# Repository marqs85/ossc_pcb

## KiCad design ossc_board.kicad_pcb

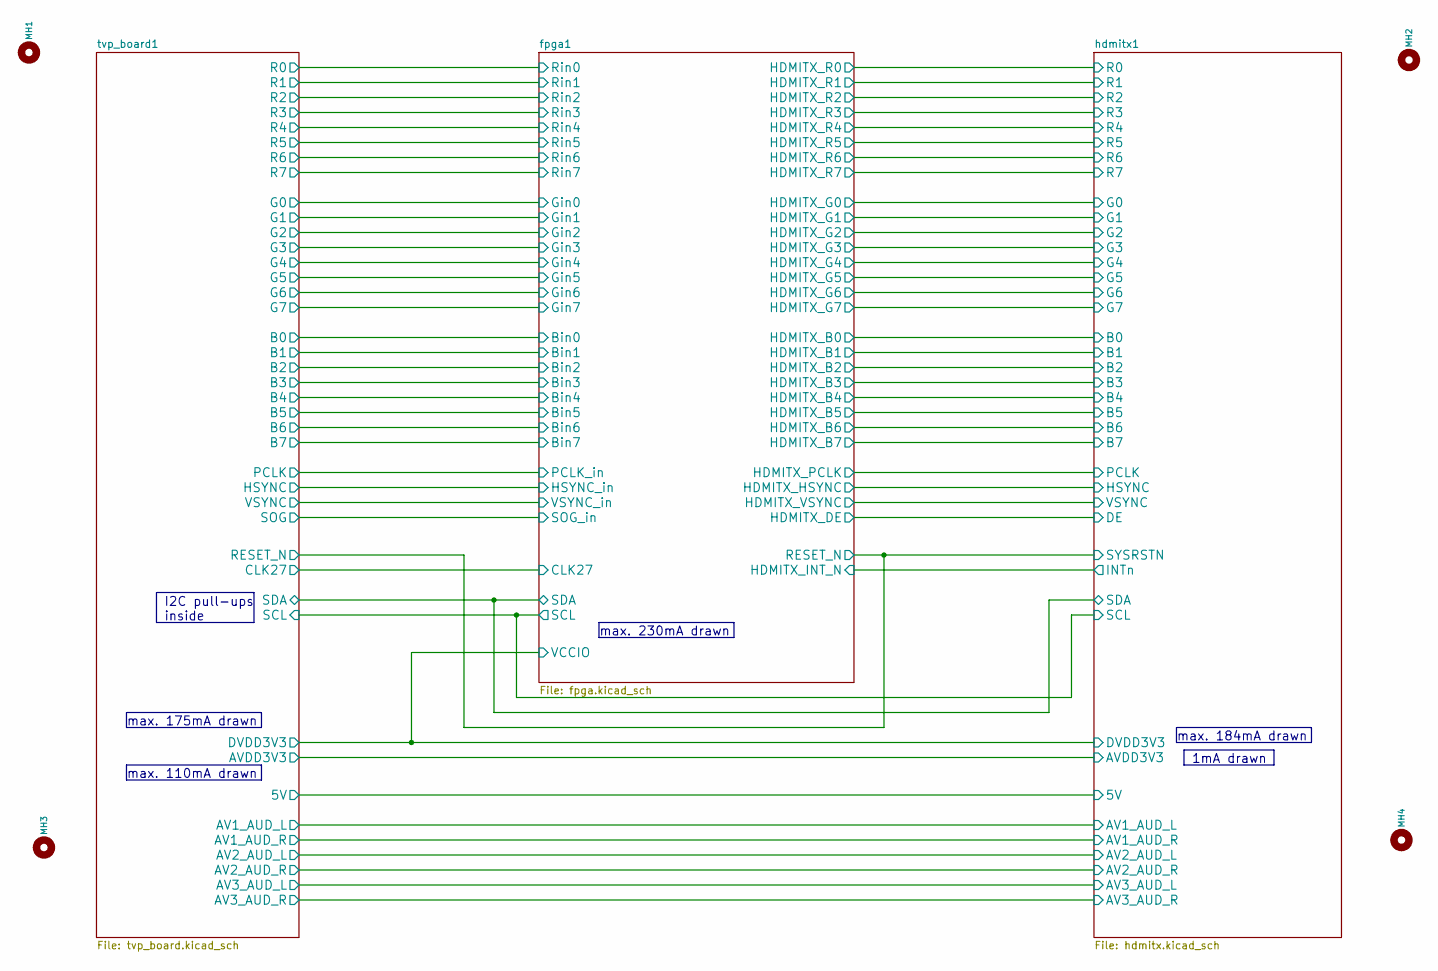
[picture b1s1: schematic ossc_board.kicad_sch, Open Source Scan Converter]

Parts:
MH1, MH2, MH3, MH4: CONN_1; 1pin

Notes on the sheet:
1mA drawn
max. 230mA drawn
max. 184mA drawn
max. 110mA drawn
max. 175mA drawn
I2C pull-ups inside

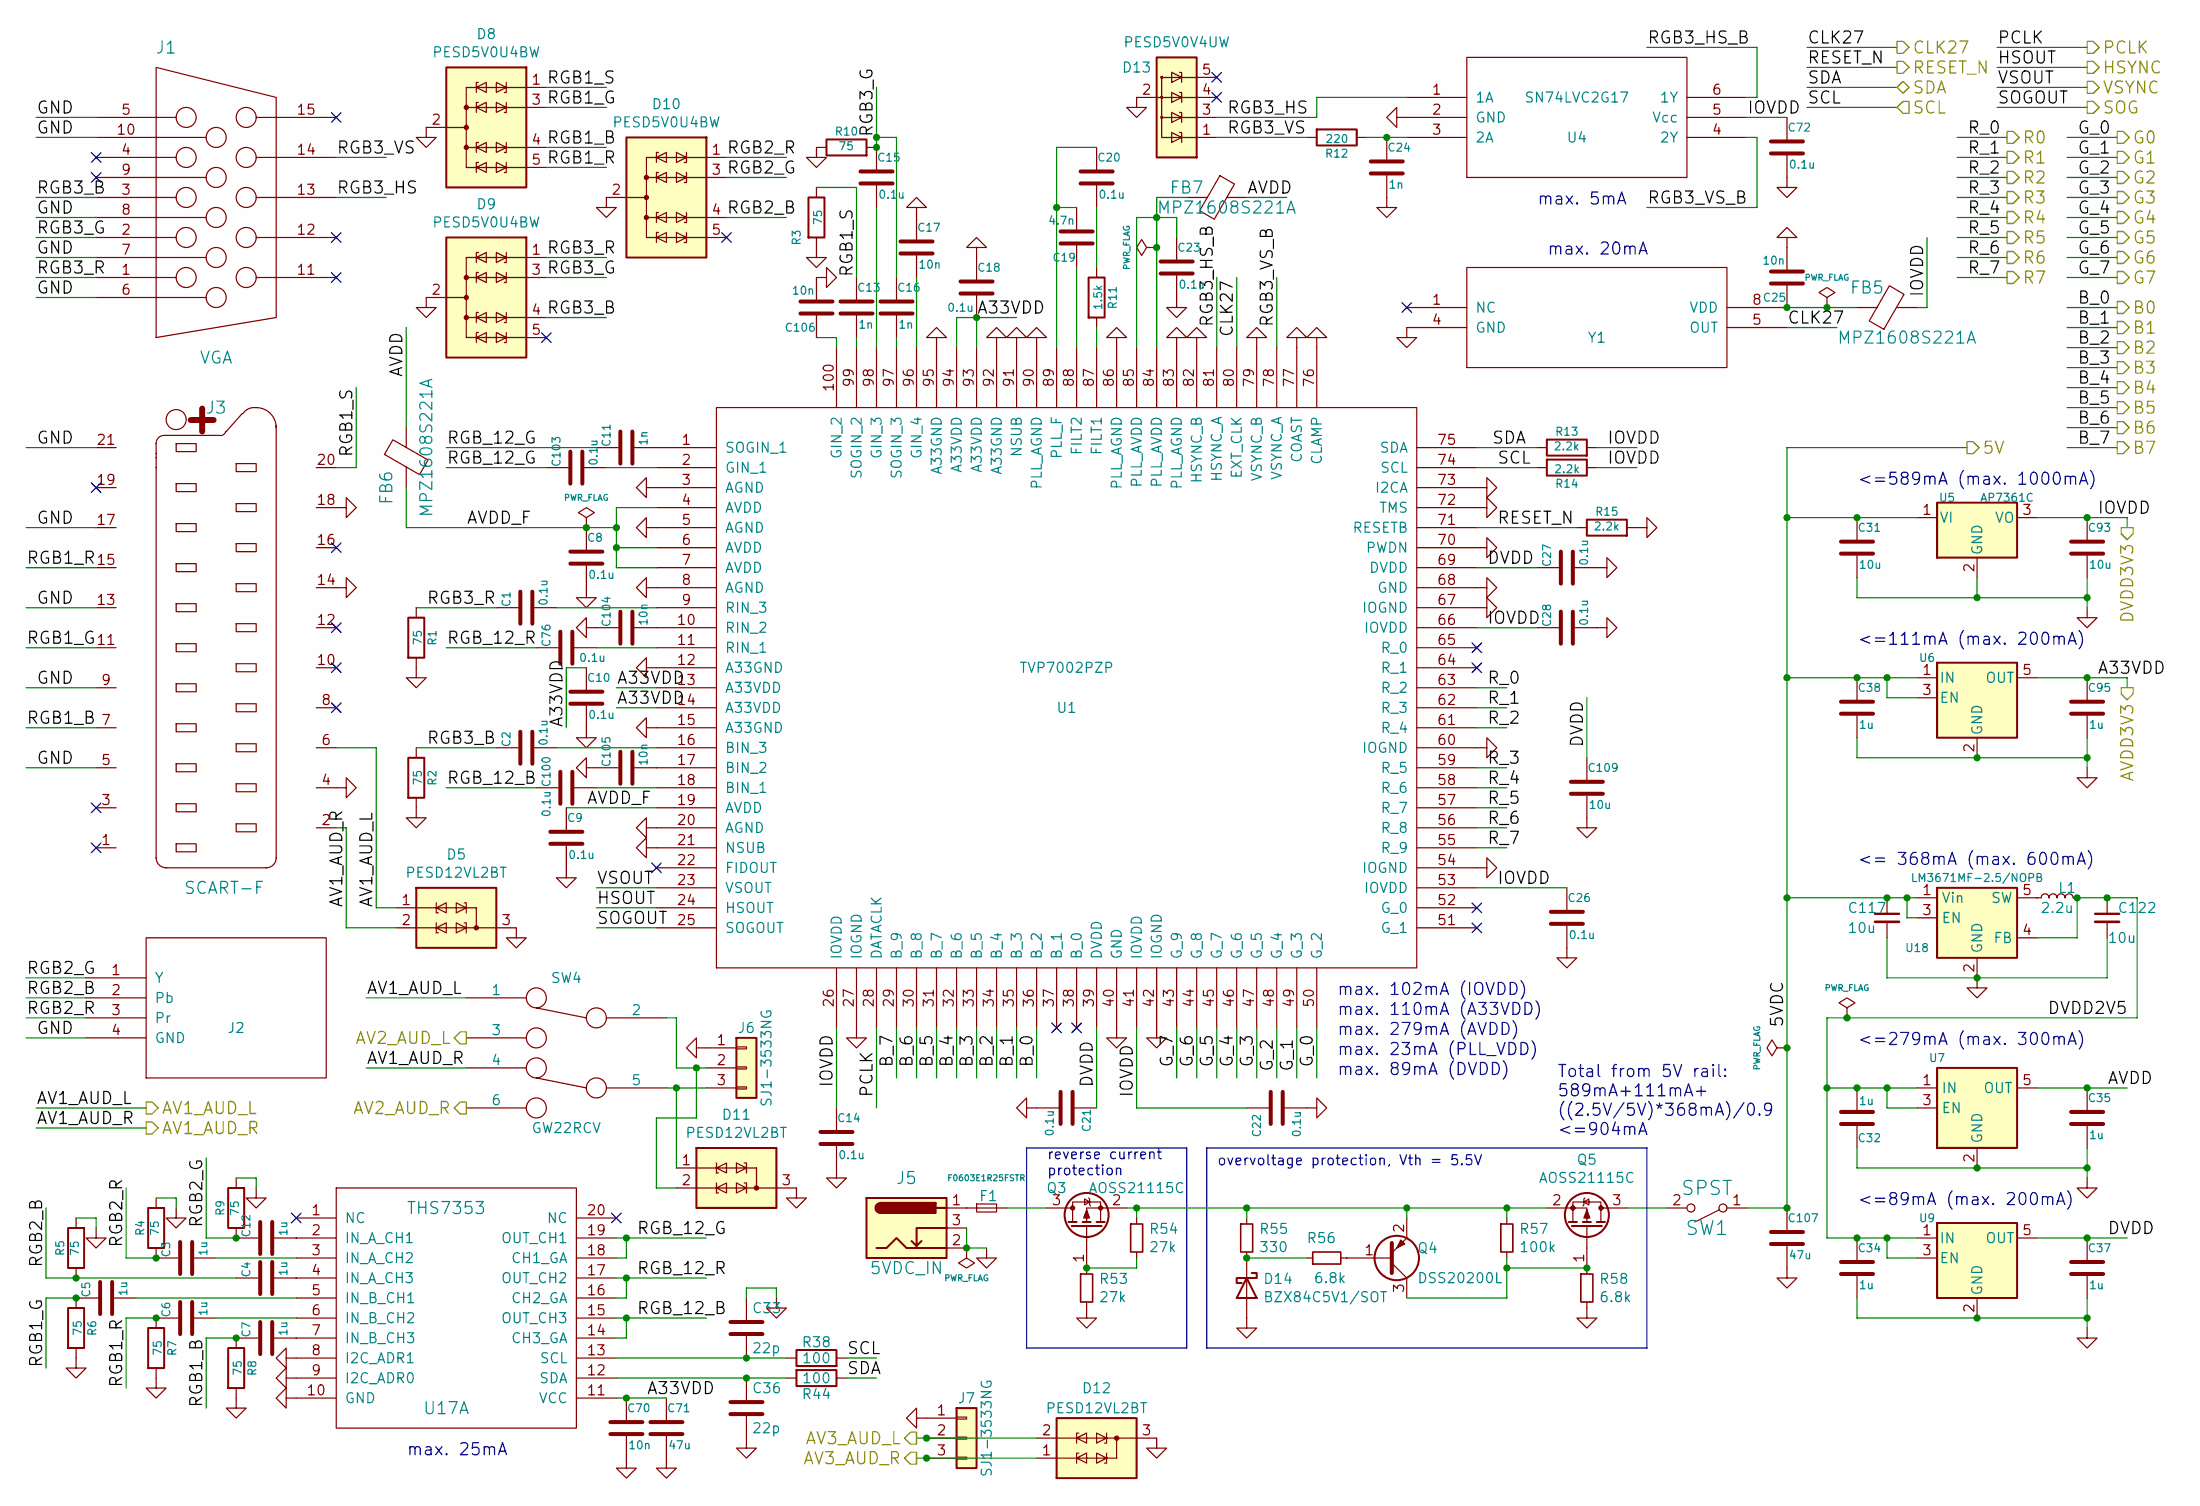
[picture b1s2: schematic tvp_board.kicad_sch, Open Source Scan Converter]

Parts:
C1, C2, C8, C9, C10, C14, C15, C18, C20, C21, C22, C23, C26, C27, C28, C72, C76, C100, C103: 0.1u; SM0603_Capa_libcms
C3, C4, C5, C6, C7, C12, C32, C34, C35, C37, C38, C95: 1u; SM0603_Capa_libcms
C11, C13, C16, C24: 1n; SM0603_Capa_libcms
C17, C25, C70, C104, C105, C106: 10n; SM0603_Capa_libcms
C19: 4.7n; SM0603_Capa_libcms
C31, C93, C109, C117, C122: 10u; SM0603_Capa_libcms
C33, C36: 22p; SM0603_Capa_libcms
C71, C107: 47u; SM0805_libcms
D5, D11, D12: PESD12VL2BT; SOT-23_Handsoldering
D8, D9, D10: PESD5V0U4BW; SOT-665
D13: PESD5V0V4UW; SOT-665
D14: BZX84C5V1/SOT; D_SOT-23_ANK
F1: F0603E1R25FSTR; SM0603_Resistor_libcms
FB5, FB6, FB7: MPZ1608S221A; SM0603_Resistor_libcms
J1: VGA; VGA_CONN
J2: (no value)
J3: SCART-F; SCART_CONN
J5: 5VDC_IN; BARREL_JACK_roundconn
J6, J7: SJ1-3533NG
L1: 2.2u; CDRH2D14
Q3, Q5: AOSS21115C; SOT-23_Handsoldering
Q4: DSS20200L; SOT-23_Handsoldering
R1, R2, R3, R4, R5, R6, R7, R8, R9, R10: 75; SM0603_Resistor_libcms
R11: 1.5k; SM0603_Resistor_libcms
R12: 220; SM0603_Resistor_libcms
R13, R14, R15: 2.2k; SM0603_Resistor_libcms
R38, R44: 100; SM0603_Resistor_libcms
R53, R54: 27k; SM0603_Resistor_libcms
R55: 330; SM0805_libcms
R56, R58: 6.8k; SM0603_Resistor_libcms
R57: 100k; SM0603_Resistor_libcms
SW1: SPST; SW_SPDT
SW4: GW22RCV; GW22RxV
U1: TVP7002PZP; TQFP-100_thermal
U4: SN74LVC2G17; SOT-23-6_Handsoldering
U5: AP7361C; SOT-223_Handsoldering
U6, U7, U9: (no value)
U17: THS7353; TSSOP-20_4.4x6.5mm_Pitch0.65mm_Handsoldering
U18: LM3671MF-2.5/NOPB; SOT-23-5_Handsoldering
Y1: (no value)

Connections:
/fpga1/CLK27: U1.80 (EXT_CLK), Y1.5 (OUT); also elsewhere on the board
/fpga1/RESET_N: R15.1, U1.71 (RESETB); also elsewhere on the board
/fpga1/SCL: R14.2, R38.2, U1.74 (SCL); also elsewhere on the board
/fpga1/SDA: R13.1, R44.1, U1.75 (SDA); also elsewhere on the board
/hdmitx1/5V: C31.1, C38.1, C107.1, C117.1, SW1.1 (A), U5.1 (VI), U6.1 (IN), U6.3 (EN), U18.1 (Vin), U18.3 (EN); also elsewhere on the board
/hdmitx1/AV1_AUD_L: D5.1 (TVS1), J3.6, SW4.1; also elsewhere on the board
/hdmitx1/AV1_AUD_R: D5.2 (TVS2), J3.2, SW4.4; also elsewhere on the board
/hdmitx1/AV2_AUD_L: SW4.3; also elsewhere on the board
/hdmitx1/AV2_AUD_R: SW4.6; also elsewhere on the board
/hdmitx1/AV3_AUD_L: D12.2 (TVS2), J7.2; also elsewhere on the board
/hdmitx1/AV3_AUD_R: D12.1 (TVS1), J7.3; also elsewhere on the board
/hdmitx1/AVDD3V3: C10.1, C18.2, C70.1, C71.1, C95.1, U1.13 (A33VDD), U1.14 (A33VDD), U1.93 (A33VDD), U1.94 (A33VDD), U6.5 (OUT), U17.11 (VCC); also elsewhere on the board
/hdmitx1/DVDD3V3: C14.1, C22.1, C26.1, C28.1, C72.1, C93.1, FB5.2, R13.2, R14.1, U1.26 (IOVDD), U1.41 (IOVDD), U1.53 (IOVDD), U1.66 (IOVDD), U4.5 (Vcc), U5.3 (VO); also elsewhere on the board
/tvp_board1/AVDD: C35.1, FB6.1, FB7.1, U7.5 (OUT)
/tvp_board1/AVDD_F: C8.1, C9.1, FB6.2, U1.4 (AVDD), U1.6 (AVDD), U1.7 (AVDD), U1.19 (AVDD)
/tvp_board1/B0: U1.36 (B_2); also elsewhere on the board
/tvp_board1/B1: U1.35 (B_3); also elsewhere on the board
/tvp_board1/B2: U1.34 (B_4); also elsewhere on the board
/tvp_board1/B3: U1.33 (B_5); also elsewhere on the board
/tvp_board1/B4: U1.32 (B_6); also elsewhere on the board
/tvp_board1/B5: U1.31 (B_7); also elsewhere on the board
/tvp_board1/B6: U1.30 (B_8); also elsewhere on the board
/tvp_board1/B7: U1.29 (B_9); also elsewhere on the board
/tvp_board1/DVDD: C21.1, C27.1, C37.1, C109.1, U1.39 (DVDD), U1.69 (DVDD), U9.5 (OUT)
/tvp_board1/DVDD2V5: C32.2, C34.1, C122.1, L1.2, U7.1 (IN), U7.3 (EN), U9.1 (IN), U9.3 (EN), U18.4 (FB)
/tvp_board1/FID: U1.22 (FIDOUT); also elsewhere on the board
/tvp_board1/G0: U1.50 (G_2); also elsewhere on the board
/tvp_board1/G1: U1.49 (G_3); also elsewhere on the board
/tvp_board1/G2: U1.48 (G_4); also elsewhere on the board
/tvp_board1/G3: U1.47 (G_5); also elsewhere on the board
/tvp_board1/G4: U1.46 (G_6); also elsewhere on the board
/tvp_board1/G5: U1.45 (G_7); also elsewhere on the board
/tvp_board1/G6: U1.44 (G_8); also elsewhere on the board
/tvp_board1/G7: U1.43 (G_9); also elsewhere on the board
/tvp_board1/HSYNC: U1.24 (HSOUT); also elsewhere on the board
/tvp_board1/PCLK: U1.28 (DATACLK); also elsewhere on the board
/tvp_board1/R0: U1.63 (R_2); also elsewhere on the board
/tvp_board1/R1: U1.62 (R_3); also elsewhere on the board
/tvp_board1/R2: U1.61 (R_4); also elsewhere on the board
/tvp_board1/R3: U1.59 (R_5); also elsewhere on the board
/tvp_board1/R4: U1.58 (R_6); also elsewhere on the board
/tvp_board1/R5: U1.57 (R_7); also elsewhere on the board
/tvp_board1/R6: U1.56 (R_8); also elsewhere on the board
/tvp_board1/R7: U1.55 (R_9); also elsewhere on the board
/tvp_board1/RGB1_B: C7.1, D8.4 (TVS3), J3.7, R8.1
/tvp_board1/RGB1_G: C5.1, D8.3 (TVS2), J3.11, R6.1
/tvp_board1/RGB1_R: C6.1, D8.5 (TVS4), J3.15, R7.1
/tvp_board1/RGB1_S: C13.1, D8.1 (TVS1), J3.20, R3.1
/tvp_board1/RGB2_B: C4.1, D10.4 (TVS3), J2.2 (Pb), R5.1
/tvp_board1/RGB2_G: C12.1, D10.3 (TVS2), J2.1 (Y), R9.1
/tvp_board1/RGB2_R: C3.1, D10.1 (TVS1), J2.3 (Pr), R4.1
/tvp_board1/RGB3_B: C2.1, D9.4 (TVS3), J1.3 (BLUE), R2.1
/tvp_board1/RGB3_G: C15.1, C16.1, D9.3 (TVS2), J1.2 (GREEN), R10.2
/tvp_board1/RGB3_HS: D13.3 (IO2), J1.13 (HSYNC), U4.1 (1A)
/tvp_board1/RGB3_HS_B: U1.81 (HSYNC_A), U4.6 (1Y)
/tvp_board1/RGB3_R: C1.1, D9.1 (TVS1), J1.1 (RED), R1.1
/tvp_board1/RGB3_VS: D13.1 (IO1), J1.14 (VSYNC), R12.2
/tvp_board1/RGB3_VS_B: U1.78 (VSYNC_A), U4.4 (2Y)
/tvp_board1/RGB_12_B: C100.1, U17.14 (CH3_GA), U17.15 (OUT_CH3)
/tvp_board1/RGB_12_G: C11.1, C103.1, U17.18 (CH1_GA), U17.19 (OUT_CH1)
/tvp_board1/RGB_12_R: C76.1, U17.16 (CH2_GA), U17.17 (OUT_CH2)
/tvp_board1/VSYNC: U1.23 (VSOUT); also elsewhere on the board
unnamed: C1.2, U1.9 (RIN_3)
unnamed: C2.2, U1.16 (BIN_3)
unnamed: C3.2, U17.3 (IN_A_CH2)
unnamed: C4.2, U17.4 (IN_A_CH3)
unnamed: C5.2, U17.5 (IN_B_CH1)
unnamed: C6.2, U17.6 (IN_B_CH2)
unnamed: C7.2, U17.7 (IN_B_CH3)
unnamed: C11.2, U1.1 (SOGIN_1)
unnamed: C12.2, U17.2 (IN_A_CH1)
unnamed: C13.2, U1.99 (SOGIN_2)
unnamed: C15.2, U1.98 (GIN_3)
unnamed: C16.2, U1.97 (SOGIN_3)
unnamed: C17.2, U1.96 (GIN_4)
unnamed: C19.1, U1.88 (FILT2)
unnamed: C19.2, C20.1, U1.89 (PLL_F)
unnamed: C20.2, R11.1
unnamed: C23.1, FB7.2, U1.84 (PLL_AVDD), U1.85 (PLL_AVDD)
unnamed: C24.1, R12.1, U4.3 (2A)
unnamed: C25.1, FB5.1, Y1.8 (VDD)
unnamed: C33.2, R38.1, U17.13 (SCL)
unnamed: C36.1, R44.2, U17.12 (SDA)
unnamed: C76.2, U1.11 (RIN_1)
unnamed: C100.2, U1.18 (BIN_1)
unnamed: C103.2, U1.2 (GIN_1)
unnamed: C104.2, U1.10 (RIN_2)
unnamed: C105.2, U1.17 (BIN_2)
unnamed: C106.1, U1.100 (GIN_2)
unnamed: D11.1 (TVS1), J6.3, SW4.5
unnamed: D11.2 (TVS2), J6.2, SW4.2
unnamed: D14.1 (K), R55.2, R56.1
unnamed: F1.1, J5.1
unnamed: F1.2, Q3.3 (D)
unnamed: L1.1, U18.5 (SW)
unnamed: Q3.1 (G), R53.1, R54.2
unnamed: Q3.2 (S), Q4.2 (E), Q5.2 (S), R54.1, R55.1, R57.1
unnamed: Q4.1 (B), R56.2
unnamed: Q4.3 (C), Q5.1 (G), R57.2, R58.1
unnamed: Q5.3 (D), SW1.2 (B)
unnamed: R11.2, U1.87 (FILT1)

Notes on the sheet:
max. 25mA
<=589mA (max. 1000mA)
max. 20mA
<=279mA (max. 300mA)
max. 279mA (AVDD)
<=111mA (max. 200mA)
max. 23mA (PLL_VDD)
max. 89mA (DVDD)
max. 110mA (A33VDD)
reverse current protection
<= 368mA (max. 600mA)
Total from 5V rail: 589mA+111mA+ ((2.5V/5V)*368mA)/0.9 <=904mA
max. 102mA (IOVDD)
max. 5mA
overvoltage protection, Vth = 5.5V
<=89mA (max. 200mA)

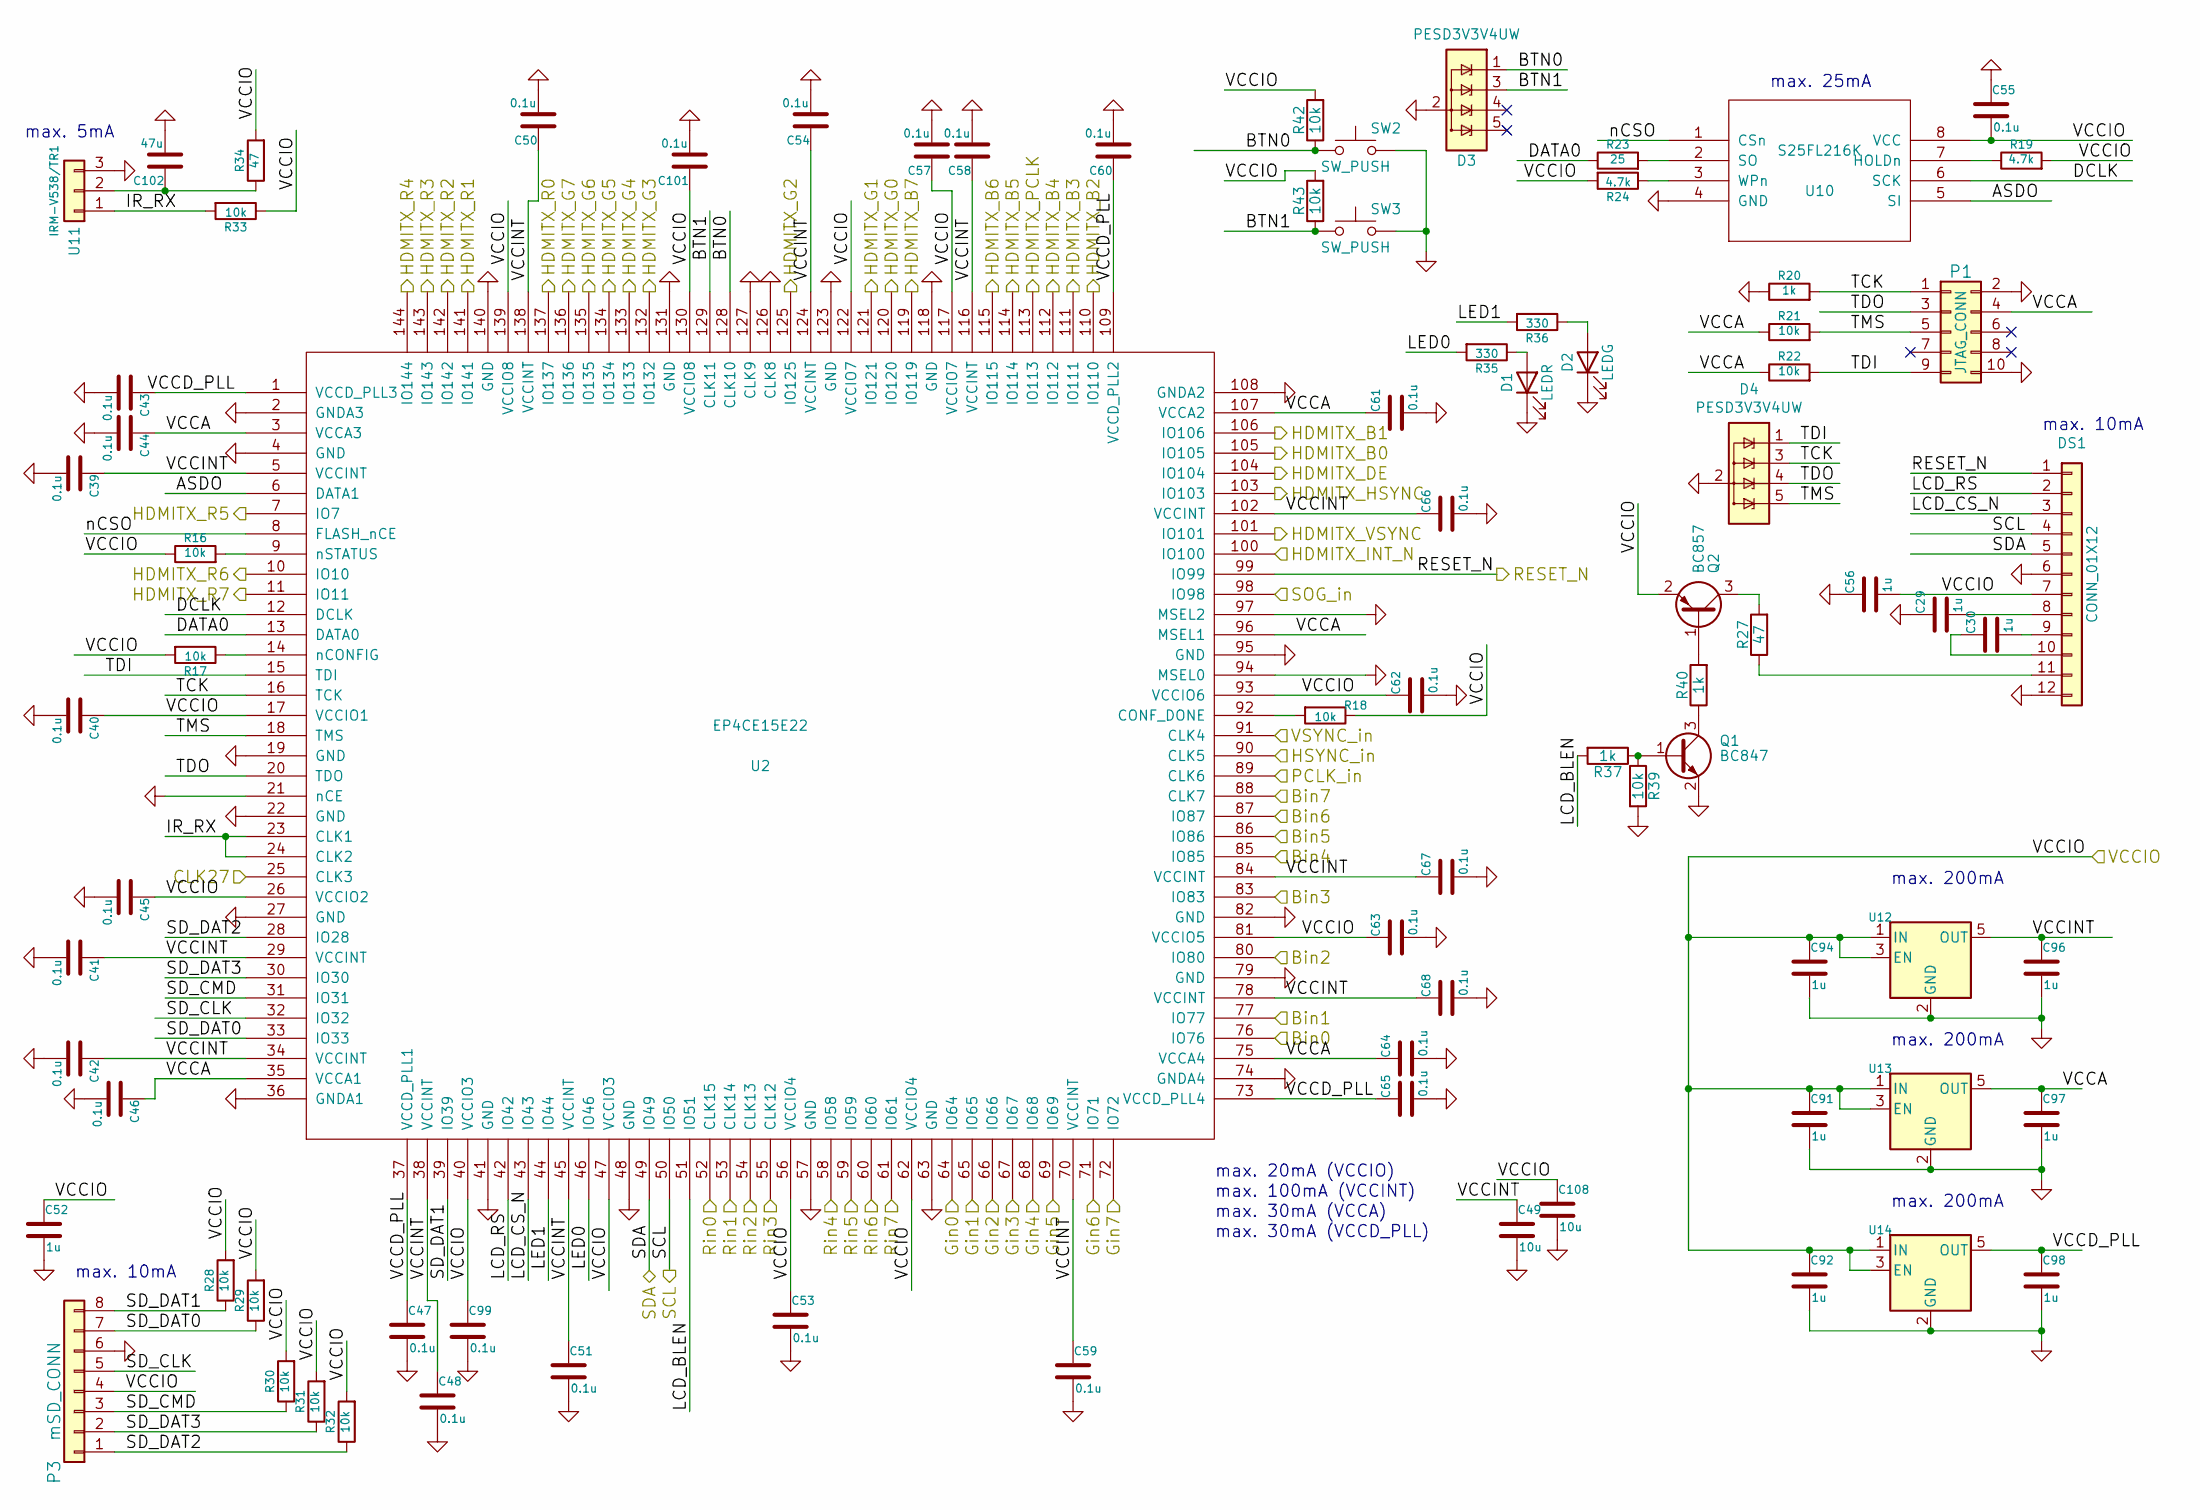
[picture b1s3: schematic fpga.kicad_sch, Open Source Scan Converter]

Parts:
C29, C30, C52, C56, C91, C92, C94, C96, C97, C98: 1u; SM0603_Capa_libcms
C39, C40, C41, C42, C43, C44, C45, C46, C47, C48, C50, C51, C53, C54, C55, C57, C58, C59, C60, C61, C62, C63, C64, C65, C66, C67, C68, C99, C101: 0.1u; SM0603_Capa_libcms
C49, C108: 10u; SM0603_Capa_libcms
C102: 47u; SM0805_libcms
D1: LEDR; LED-0603
D2: LEDG; LED-0603
D3, D4: PESD3V3V4UW; SOT-665
DS1: CONN_01X12; NHD-C0216CZ_vertmount
P1: JTAG_CONN; VASCH5x2
P3: mSD_CONN; DM3D-SF; Part ID DM3D-SF
Q1: BC847; SOT-23_Handsoldering
Q2: BC857; SOT-23_Handsoldering
R16, R17, R18, R21, R22, R28, R29, R30, R31, R32, R33, R39, R42, R43: 10k; SM0603_Resistor_libcms
R19, R24: 4.7k; SM0603_Resistor_libcms
R20, R37, R40: 1k; SM0603_Resistor_libcms
R23: 25; SM0603_Resistor_libcms
R27, R34: 47; SM0603_Resistor_libcms
R35, R36: 330; SM0603_Resistor_libcms
SW2, SW3: SW_PUSH; SW_PUSH-SKHCBFA010
U2: EP4CE15E22; TQFP-144_thermal
U10: S25FL216K; SOIC-8_3.9x4.9mm_Pitch1.27mm_Handsoldering
U11: IRM-V538/TR1; IRM-V5XX_TR1
U12, U13, U14: (no value)

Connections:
/fpga1/ASDO: U2.6 (DATA1), U10.5 (SI)
/fpga1/BTN0: D3.1 (IO1), R42.1, SW2.1, U2.128 (CLK10)
/fpga1/BTN1: D3.3 (IO2), R43.1, SW3.1, U2.129 (CLK11)
/fpga1/CLK27: U2.25 (CLK3); also elsewhere on the board
/fpga1/DATA0: R23.1, U2.13 (DATA0)
/fpga1/DCLK: U2.12 (DCLK), U10.6 (SCK)
/fpga1/HDMITX_HSYNC: U2.103 (IO103); also elsewhere on the board
/fpga1/HDMITX_INT_N: U2.100 (IO100); also elsewhere on the board
/fpga1/HDMITX_PCLK: U2.113 (IO113); also elsewhere on the board
/fpga1/HDMITX_R0: U2.137 (IO137); also elsewhere on the board
/fpga1/HDMITX_R1: U2.141 (IO141); also elsewhere on the board
/fpga1/HDMITX_R2: U2.142 (IO142); also elsewhere on the board
/fpga1/HDMITX_R3: U2.143 (IO143); also elsewhere on the board
/fpga1/HDMITX_R4: U2.144 (IO144); also elsewhere on the board
/fpga1/HDMITX_R5: U2.7 (IO7); also elsewhere on the board
/fpga1/HDMITX_R6: U2.10 (IO10); also elsewhere on the board
/fpga1/HDMITX_R7: U2.11 (IO11); also elsewhere on the board
/fpga1/HDMITX_VSYNC: U2.101 (IO101); also elsewhere on the board
/fpga1/LCD_BLEN: R37.2, U2.51 (IO51)
/fpga1/LCD_CS_N: DS1.3, U2.43 (IO43)
/fpga1/LCD_RS: DS1.2, U2.42 (IO42)
/fpga1/LED0: R35.2, U2.46 (IO46)
/fpga1/LED1: R36.2, U2.44 (IO44)
/fpga1/RESET_N: DS1.1, U2.99 (IO99); also elsewhere on the board
/fpga1/SCL: DS1.4, U2.50 (IO50); also elsewhere on the board
/fpga1/SDA: DS1.5, U2.49 (IO49); also elsewhere on the board
/fpga1/SD_CLK: P3.5, U2.32 (IO32)
/fpga1/SD_CMD: P3.3, R30.1, U2.31 (IO31)
/fpga1/SD_DAT0: P3.7, R29.1, U2.33 (IO33)
/fpga1/SD_DAT1: P3.8, R28.1, U2.39 (IO39)
/fpga1/SD_DAT2: P3.1, R32.1, U2.28 (IO28)
/fpga1/SD_DAT3: P3.2, R31.1, U2.30 (IO30)
/fpga1/TCK: D4.3 (IO2), P1.1, R20.2, U2.16 (TCK)
/fpga1/TDI: D4.1 (IO1), P1.9, R22.2, U2.15 (TDI)
/fpga1/TDO: D4.4 (IO3), P1.3, U2.20 (TDO)
/fpga1/TMS: D4.5 (IO4), P1.5, R21.2, U2.18 (TMS)
/fpga1/VCCA: C44.1, C46.1, C61.1, C64.1, C97.1, P1.4, R21.1, R22.1, U2.3 (VCCA3), U2.35 (VCCA1), U2.75 (VCCA4), U2.96 (MSEL1), U2.107 (VCCA2), U13.5 (OUT)
/fpga1/VCCD_PLL: C43.1, C47.1, C60.1, C65.1, C98.1, U2.1 (VCCD_PLL3), U2.37 (VCCD_PLL1), U2.73 (VCCD_PLL4), U2.109 (VCCD_PLL2), U14.5 (OUT)
/fpga1/VCCINT: C39.1, C41.1, C42.1, C48.1, C49.1, C50.1, C51.1, C54.1, C58.1, C59.1, C66.1, C67.1, C68.1, C96.1, U2.5 (VCCINT), U2.29 (VCCINT), U2.34 (VCCINT), U2.38 (VCCINT), U2.45 (VCCINT), U2.70 (VCCINT), U2.78 (VCCINT), U2.84 (VCCINT), U2.102 (VCCINT), U2.116 (VCCINT), U2.124 (VCCINT), U2.138 (VCCINT), U12.5 (OUT)
/fpga1/nCSO: U2.8 (FLASH_nCE), U10.1 (CSn)
/hdmitx1/B0: U2.105 (IO105); also elsewhere on the board
/hdmitx1/B1: U2.106 (IO106); also elsewhere on the board
/hdmitx1/B2: U2.110 (IO110); also elsewhere on the board
/hdmitx1/B3: U2.111 (IO111); also elsewhere on the board
/hdmitx1/B4: U2.112 (IO112); also elsewhere on the board
/hdmitx1/B5: U2.114 (IO114); also elsewhere on the board
/hdmitx1/B6: U2.115 (IO115); also elsewhere on the board
/hdmitx1/B7: U2.119 (IO119); also elsewhere on the board
/hdmitx1/DE: U2.104 (IO104); also elsewhere on the board
/hdmitx1/DVDD3V3: C40.1, C45.1, C52.1, C53.1, C55.2, C56.2, C57.1, C62.1, C63.1, C91.1, C92.1, C94.1, C99.1, C101.1, C108.1, DS1.7, P3.4, Q2.2 (E), R16.1, R17.2, R18.1, R19.2, R24.2, R28.2, R29.2, R30.2, R31.2, R32.2, R33.1, R34.2, R42.2, R43.2, U2.17 (VCCIO1), U2.26 (VCCIO2), U2.40 (VCCIO3), U2.47 (VCCIO3), U2.56 (VCCIO4), U2.62 (VCCIO4), U2.81 (VCCIO5), U2.93 (VCCIO6), U2.117 (VCCIO7), U2.122 (VCCIO7), U2.130 (VCCIO8), U2.139 (VCCIO8), U10.8 (VCC), U12.1 (IN), U12.3 (EN), U13.1 (IN), U13.3 (EN), U14.1 (IN), U14.3 (EN); also elsewhere on the board
/hdmitx1/G0: U2.120 (IO120); also elsewhere on the board
/hdmitx1/G1: U2.121 (IO121); also elsewhere on the board
/hdmitx1/G2: U2.125 (IO125); also elsewhere on the board
/hdmitx1/G3: U2.132 (IO132); also elsewhere on the board
/hdmitx1/G4: U2.133 (IO133); also elsewhere on the board
/hdmitx1/G5: U2.134 (IO134); also elsewhere on the board
/hdmitx1/G6: U2.135 (IO135); also elsewhere on the board
/hdmitx1/G7: U2.136 (IO136); also elsewhere on the board
/tvp_board1/B0: U2.76 (IO76); also elsewhere on the board
/tvp_board1/B1: U2.77 (IO77); also elsewhere on the board
/tvp_board1/B2: U2.80 (IO80); also elsewhere on the board
/tvp_board1/B3: U2.83 (IO83); also elsewhere on the board
/tvp_board1/B4: U2.85 (IO85); also elsewhere on the board
/tvp_board1/B5: U2.86 (IO86); also elsewhere on the board
/tvp_board1/B6: U2.87 (IO87); also elsewhere on the board
/tvp_board1/B7: U2.88 (CLK7); also elsewhere on the board
/tvp_board1/FID: U2.98 (IO98); also elsewhere on the board
/tvp_board1/G0: U2.64 (IO64); also elsewhere on the board
/tvp_board1/G1: U2.65 (IO65); also elsewhere on the board
/tvp_board1/G2: U2.66 (IO66); also elsewhere on the board
/tvp_board1/G3: U2.67 (IO67); also elsewhere on the board
/tvp_board1/G4: U2.68 (IO68); also elsewhere on the board
/tvp_board1/G5: U2.69 (IO69); also elsewhere on the board
/tvp_board1/G6: U2.71 (IO71); also elsewhere on the board
/tvp_board1/G7: U2.72 (IO72); also elsewhere on the board
/tvp_board1/HSYNC: U2.90 (CLK5); also elsewhere on the board
/tvp_board1/PCLK: U2.89 (CLK6); also elsewhere on the board
/tvp_board1/R0: U2.52 (CLK15); also elsewhere on the board
/tvp_board1/R1: U2.53 (CLK14); also elsewhere on the board
/tvp_board1/R2: U2.54 (CLK13); also elsewhere on the board
/tvp_board1/R3: U2.55 (CLK12); also elsewhere on the board
/tvp_board1/R4: U2.58 (IO58); also elsewhere on the board
/tvp_board1/R5: U2.59 (IO59); also elsewhere on the board
/tvp_board1/R6: U2.60 (IO60); also elsewhere on the board
/tvp_board1/R7: U2.61 (IO61); also elsewhere on the board
/tvp_board1/VSYNC: U2.91 (CLK4); also elsewhere on the board
unnamed: C29.2, DS1.8
unnamed: C30.1, DS1.10
unnamed: C30.2, DS1.9
unnamed: C102.1, R34.1, U11.2
unnamed: D1.2 (A), R35.1
unnamed: D2.2 (A), R36.1
unnamed: DS1.11, R27.1
unnamed: Q1.1 (B), R37.1, R39.1
unnamed: Q1.3 (C), R40.1
unnamed: Q2.1 (B), R40.2
unnamed: Q2.3 (C), R27.2
unnamed: R16.2, U2.9 (nSTATUS)
unnamed: R17.1, U2.14 (nCONFIG)
unnamed: R18.2, U2.92 (CONF_DONE)
unnamed: R19.1, U10.7 (HOLDn)
unnamed: R23.2, U10.2 (SO)
unnamed: R24.1, U10.3 (WPn)

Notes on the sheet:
max. 200mA
max. 10mA
max. 100mA (VCCINT)
max. 25mA
max. 20mA (VCCIO)
max. 5mA
max. 30mA (VCCD_PLL)
max. 30mA (VCCA)

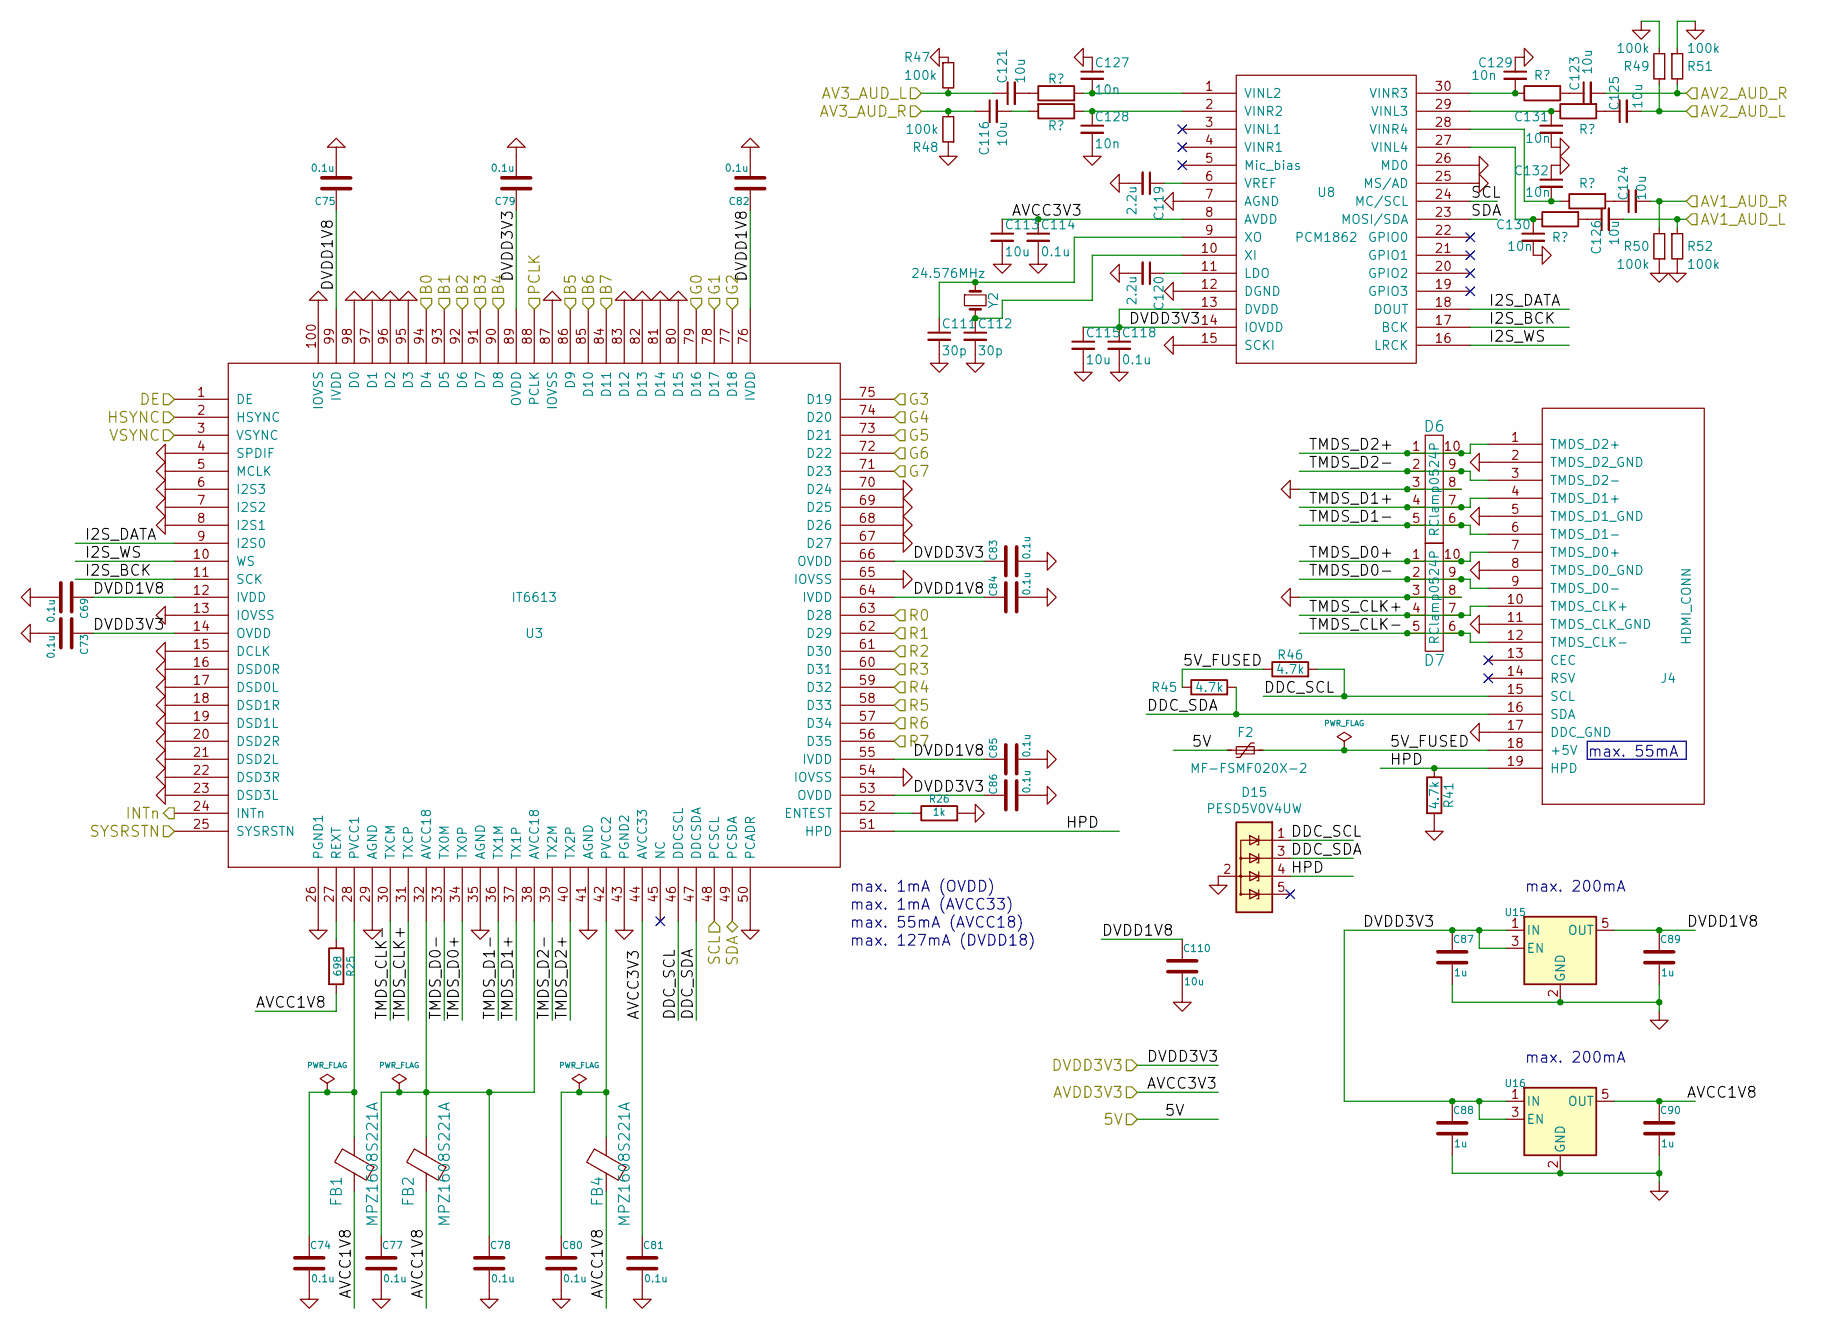
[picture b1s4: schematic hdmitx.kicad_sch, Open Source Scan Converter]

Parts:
C69, C73, C74, C75, C77, C78, C79, C80, C81, C82, C83, C84, C85, C86, C114, C118: 0.1u; SM0603_Capa_libcms
C87, C88, C89, C90: 1u; SM0603_Capa_libcms
C110, C113, C115, C116, C121, C123, C124, C125, C126: 10u; SM0603_Capa_libcms
C111, C112: 30p; SM0603_Capa_libcms
C119, C120: 2.2u; SM0603_Capa_libcms
C127, C128, C129, C130, C131, C132: 10n; SM0603_Capa_libcms
D6, D7: RClamp0524P; SLP2510P8
D15: PESD5V0V4UW; SOT-665
F2: MF-FSMF020X-2; SM0603_Resistor_libcms
FB1, FB2, FB4: MPZ1608S221A; SM0603_Resistor_libcms
J4: HDMI_CONN; HDMI_CONN-10029449-111RLF; Part ID 10029449-111RLF
R25: 698; SM0603_Resistor_libcms
R26: 1k; SM0603_Resistor_libcms
R41, R45, R46: 4.7k; SM0603_Resistor_libcms
R47, R48, R49, R50, R51, R52: 100k; SM0603_Resistor_libcms
U3: IT6613; TQFP-100_custom
U8: PCM1862; TSSOP-30_4.4x7.8mm_Pitch0.5mm_Handsoldering
U15, U16: (no value)
Y2: 24.576MHz; ECS-3X9X

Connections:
/fpga1/HDMITX_HSYNC: U3.2 (HSYNC); also elsewhere on the board
/fpga1/HDMITX_INT_N: U3.24 (INTn); also elsewhere on the board
/fpga1/HDMITX_PCLK: U3.88 (PCLK); also elsewhere on the board
/fpga1/HDMITX_R0: U3.63 (D28); also elsewhere on the board
/fpga1/HDMITX_R1: U3.62 (D29); also elsewhere on the board
/fpga1/HDMITX_R2: U3.61 (D30); also elsewhere on the board
/fpga1/HDMITX_R3: U3.60 (D31); also elsewhere on the board
/fpga1/HDMITX_R4: U3.59 (D32); also elsewhere on the board
/fpga1/HDMITX_R5: U3.58 (D33); also elsewhere on the board
/fpga1/HDMITX_R6: U3.57 (D34); also elsewhere on the board
/fpga1/HDMITX_R7: U3.56 (D35); also elsewhere on the board
/fpga1/HDMITX_VSYNC: U3.3 (VSYNC); also elsewhere on the board
/fpga1/RESET_N: U3.25 (SYSRSTN); also elsewhere on the board
/fpga1/SCL: U3.48 (PCSCL), U8.24 (MC/SCL); also elsewhere on the board
/fpga1/SDA: U3.49 (PCSDA), U8.23 (MOSI/SDA); also elsewhere on the board
/hdmitx1/5V: F2.1; also elsewhere on the board
/hdmitx1/5V_FUSED: F2.2, J4.18 (+5V), R45.1, R46.1
/hdmitx1/AV1_AUD_L: C126.2, R52.1; also elsewhere on the board
/hdmitx1/AV1_AUD_R: C124.2, R50.2; also elsewhere on the board
/hdmitx1/AV2_AUD_L: C125.2, R49.1; also elsewhere on the board
/hdmitx1/AV2_AUD_R: C123.2, R51.2; also elsewhere on the board
/hdmitx1/AV3_AUD_L: C121.1, R47.2; also elsewhere on the board
/hdmitx1/AV3_AUD_R: C116.1, R48.2; also elsewhere on the board
/hdmitx1/AVCC1V8: C90.1, FB1.1, FB2.1, FB4.1, R25.2, U16.5 (OUT)
/hdmitx1/AVDD3V3: C81.1, C113.1, C114.1, U3.44 (AVCC33), U8.8 (AVDD); also elsewhere on the board
/hdmitx1/B0: U3.94 (D4); also elsewhere on the board
/hdmitx1/B1: U3.93 (D5); also elsewhere on the board
/hdmitx1/B2: U3.92 (D6); also elsewhere on the board
/hdmitx1/B3: U3.91 (D7); also elsewhere on the board
/hdmitx1/B4: U3.90 (D8); also elsewhere on the board
/hdmitx1/B5: U3.86 (D9); also elsewhere on the board
/hdmitx1/B6: U3.85 (D10); also elsewhere on the board
/hdmitx1/B7: U3.84 (D11); also elsewhere on the board
/hdmitx1/DDC_SCL: D15.1 (IO1), J4.15 (SCL), R46.2, U3.46 (DDCSCL)
/hdmitx1/DDC_SDA: D15.3 (IO2), J4.16 (SDA), R45.2, U3.47 (DDCSDA)
/hdmitx1/DE: U3.1 (DE); also elsewhere on the board
/hdmitx1/DVDD1V8: C69.1, C75.1, C82.1, C84.1, C85.1, C89.1, C110.1, U3.12 (IVDD), U3.55 (IVDD), U3.64 (IVDD), U3.76 (IVDD), U3.99 (IVDD), U15.5 (OUT)
/hdmitx1/DVDD3V3: C73.1, C79.1, C83.1, C86.1, C87.1, C88.1, C115.1, C118.1, U3.14 (OVDD), U3.53 (OVDD), U3.66 (OVDD), U3.89 (OVDD), U8.13 (DVDD), U8.14 (IOVDD), U15.1 (IN), U15.3 (EN), U16.1 (IN), U16.3 (EN); also elsewhere on the board
/hdmitx1/G0: U3.79 (D16); also elsewhere on the board
/hdmitx1/G1: U3.78 (D17); also elsewhere on the board
/hdmitx1/G2: U3.77 (D18); also elsewhere on the board
/hdmitx1/G3: U3.75 (D19); also elsewhere on the board
/hdmitx1/G4: U3.74 (D20); also elsewhere on the board
/hdmitx1/G5: U3.73 (D21); also elsewhere on the board
/hdmitx1/G6: U3.72 (D22); also elsewhere on the board
/hdmitx1/G7: U3.71 (D23); also elsewhere on the board
/hdmitx1/HPD: D15.4 (IO3), J4.19 (HPD), R41.1, U3.51 (HPD)
/hdmitx1/I2S_BCK: U3.11 (SCK), U8.17 (BCK)
/hdmitx1/I2S_DATA: U3.9 (I2S0), U8.18 (DOUT)
/hdmitx1/I2S_WS: U3.10 (WS), U8.16 (LRCK)
/hdmitx1/TMDS_CLK+: D7.4, D7.7, J4.10 (TMDS_CLK+), U3.31 (TXCP)
/hdmitx1/TMDS_CLK-: D7.5, D7.6, J4.12 (TMDS_CLK-), U3.30 (TXCM)
/hdmitx1/TMDS_D0+: D7.1, D7.10, J4.7 (TMDS_D0+), U3.34 (TX0P)
/hdmitx1/TMDS_D0-: D7.2, D7.9, J4.9 (TMDS_D0-), U3.33 (TX0M)
/hdmitx1/TMDS_D1+: D6.4, D6.7, J4.4 (TMDS_D1+), U3.37 (TX1P)
/hdmitx1/TMDS_D1-: D6.5, D6.6, J4.6 (TMDS_D1-), U3.36 (TX1M)
/hdmitx1/TMDS_D2+: D6.1, D6.10, J4.1 (TMDS_D2+), U3.40 (TX2P)
/hdmitx1/TMDS_D2-: D6.2, D6.9, J4.3 (TMDS_D2-), U3.39 (TX2M)
unnamed: C74.1, FB1.2, U3.28 (PVCC1)
unnamed: C77.1, C78.1, FB2.2, U3.32 (AVCC18), U3.38 (AVCC18)
unnamed: C80.1, FB4.2, U3.42 (PVCC2)
unnamed: C111.1, U8.9 (XO), Y2.1
unnamed: C112.1, U8.10 (XI), Y2.2
unnamed 168: C116.2; also elsewhere on the board
unnamed: C119.1, U8.6 (VREF)
unnamed: C120.1, U8.11 (LDO)
unnamed 171: C121.2; also elsewhere on the board
unnamed 172: C123.1; also elsewhere on the board
unnamed 173: C124.1; also elsewhere on the board
unnamed 174: C125.1; also elsewhere on the board
unnamed 175: C126.1; also elsewhere on the board
unnamed 176: C127.2, U8.1 (VINL2); also elsewhere on the board
unnamed 177: C128.1, U8.2 (VINR2); also elsewhere on the board
unnamed 178: C129.2, U8.30 (VINR3); also elsewhere on the board
unnamed 179: C130.1, U8.27 (VINL4); also elsewhere on the board
unnamed 180: C131.1, U8.29 (VINL3); also elsewhere on the board
unnamed 181: C132.2, U8.28 (VINR4); also elsewhere on the board
unnamed: R25.1, U3.27 (REXT)
unnamed: R26.1, U3.52 (ENTEST)

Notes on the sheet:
max. 200mA
max. 1mA (AVCC33)
max. 127mA (DVDD18)
max. 1mA (OVDD)
max. 55mA
max. 55mA (AVCC18)

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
